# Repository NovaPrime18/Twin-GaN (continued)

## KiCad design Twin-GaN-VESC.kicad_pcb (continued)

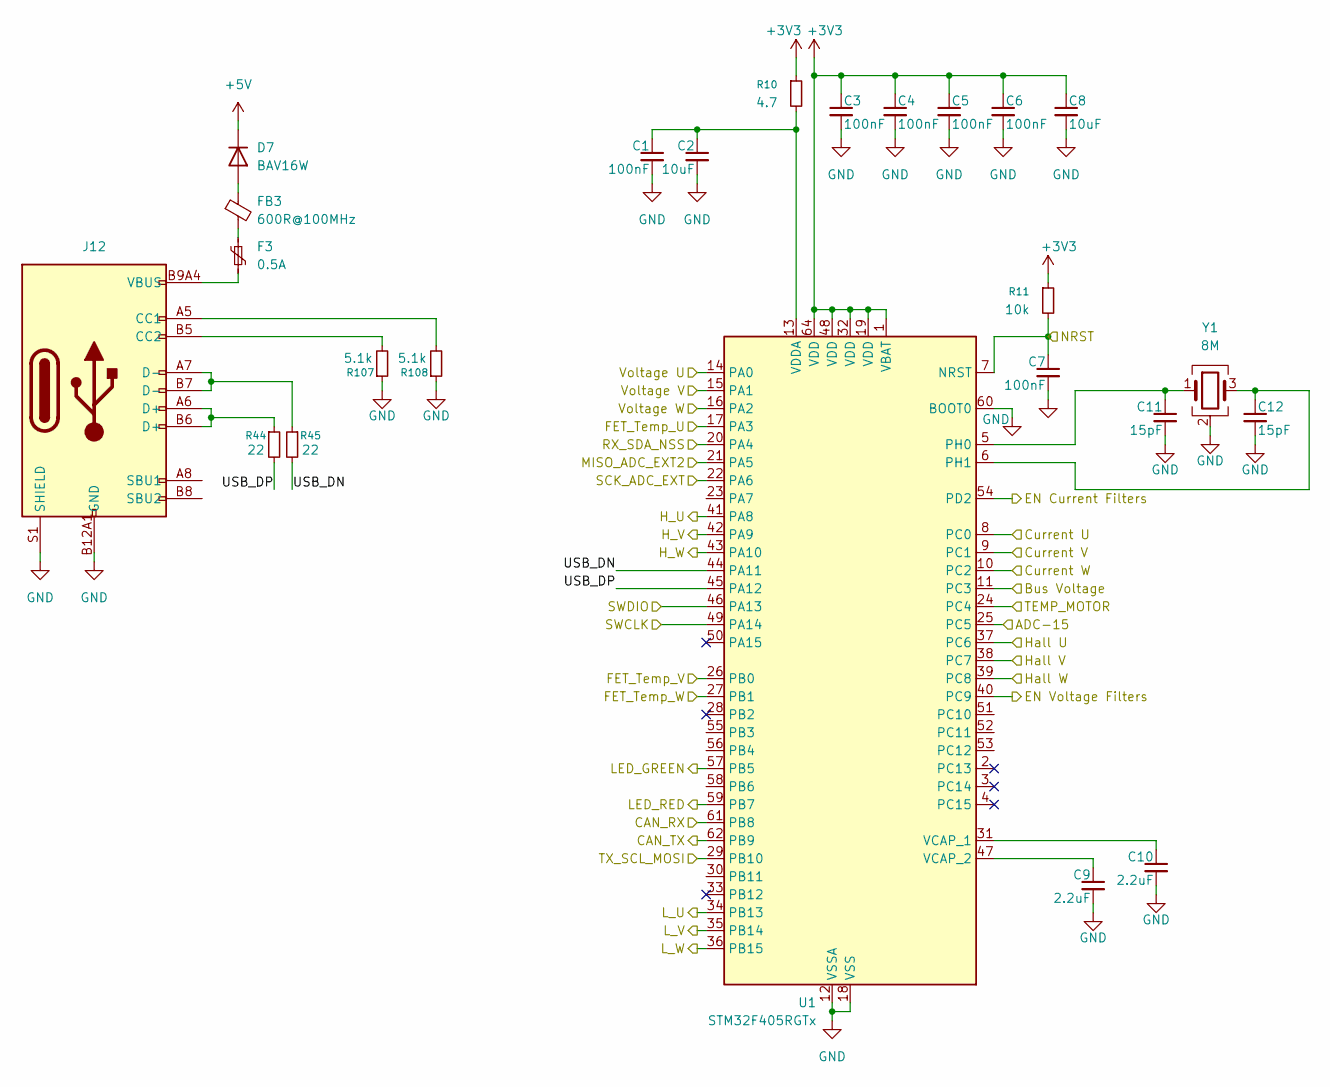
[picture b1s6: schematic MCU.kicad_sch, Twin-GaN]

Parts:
C1, C3, C4, C5, C6, C7: 100nF; C_0402_1005Metric; LCSC C307331
C2, C8: 10uF; C_0805_2012Metric; LCSC C440198
C9, C10: 2.2uF; C_0402_1005Metric; LCSC C20539421
C11, C12: 15pF; C_0402_1005Metric; LCSC C1548
D7: BAV16W; D_SOD-123; JLC C459527
F3: 0.5A; R_0805_2012Metric; JLC C2833485
FB3: 600R@100MHz; L_0402_1005Metric; LCSC C76884
J12: Connector, USB-TYPE-C-16P; TYPE-C-SMD_HX-TYPE-C-16PIN; LCSC C2927039
R10: 4.7; R_0402_1005Metric; LCSC C25121
R11: 10k; R_0402_1005Metric; LCSC C25744
R44, R45: 22; R_0402_1005Metric; LCSC C25092
R107, R108: 5.1k; R_0402_1005Metric; LCSC C25905
U1: STM32F405RGTx; LQFP-64_10x10mm_P0.5mm; LCSC C15742
Y1: 8M; Crystal_SMD_3225-4Pin_3.2x2.5mm; JLC C2682775

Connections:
+3V3: C3.1, C4.1, C5.1, C6.1, C8.1, R10.1, R11.1, U1.1 (VBAT), U1.19 (VDD), U1.32 (VDD), U1.48 (VDD), U1.64 (VDD); also elsewhere on the board
+5V: D7.1 (K); also elsewhere on the board
/Bus Voltage: U1.11 (PC3); also elsewhere on the board
/CAN1/RX: U1.61 (PB8); also elsewhere on the board
/CAN1/TX: U1.62 (PB9); also elsewhere on the board
/Filters/Curr_U_Out: U1.8 (PC0); also elsewhere on the board
/Filters/Curr_V_Out: U1.9 (PC1); also elsewhere on the board
/Filters/Curr_W_Out: U1.10 (PC2); also elsewhere on the board
/Filters/EN_C: U1.54 (PD2); also elsewhere on the board
/Filters/EN_V: U1.40 (PC9); also elsewhere on the board
/Filters/Volt_U_In: U1.14 (PA0); also elsewhere on the board
/Filters/Volt_V_In: U1.15 (PA1); also elsewhere on the board
/Filters/Volt_W_In: U1.16 (PA2); also elsewhere on the board
/MCU/ADC-15: U1.25 (PC5); also elsewhere on the board
/MCU/FET_Temp_U: U1.17 (PA3); also elsewhere on the board
/MCU/FET_Temp_V: U1.26 (PB0); also elsewhere on the board
/MCU/FET_Temp_W: U1.27 (PB1); also elsewhere on the board
/MCU/H_U: U1.41 (PA8); also elsewhere on the board
/MCU/H_V: U1.42 (PA9); also elsewhere on the board
/MCU/H_W: U1.43 (PA10); also elsewhere on the board
/MCU/Hall U: U1.37 (PC6); also elsewhere on the board
/MCU/Hall V: U1.38 (PC7); also elsewhere on the board
/MCU/Hall W: U1.39 (PC8); also elsewhere on the board
/MCU/LED_GREEN: U1.57 (PB5); also elsewhere on the board
/MCU/LED_RED: U1.59 (PB7); also elsewhere on the board
/MCU/L_U: U1.34 (PB13); also elsewhere on the board
/MCU/L_V: U1.35 (PB14); also elsewhere on the board
/MCU/L_W: U1.36 (PB15); also elsewhere on the board
/MCU/MISO_ADC_EXT2: U1.21 (PA5); also elsewhere on the board
/MCU/NRST: C7.1, R11.2, U1.7 (NRST); also elsewhere on the board
/MCU/RX_SDA_NSS: U1.20 (PA4); also elsewhere on the board
/MCU/SCK_ADC_EXT: U1.22 (PA6); also elsewhere on the board
/MCU/SWCLK: U1.49 (PA14); also elsewhere on the board
/MCU/SWDIO: U1.46 (PA13); also elsewhere on the board
/MCU/TEMP_MOTOR: U1.24 (PC4); also elsewhere on the board
/MCU/TX_SCL_MOSI: U1.29 (PB10); also elsewhere on the board
/MCU/USB_DN: R45.2, U1.44 (PA11)
/MCU/USB_DP: R44.2, U1.45 (PA12)
GND: C1.2, C2.2, C3.2, C4.2, C5.2, C6.2, C7.2, C8.2, C9.2, C10.2, C11.2, C12.2, J12.A12B1 (GND), J12.B12A1 (GND), J12.S1 (SHIELD), R107.1, R108.1, U1.12 (VSSA), U1.18 (VSS), U1.60 (BOOT0), U1.63 (VSS), Y1.2 (G), Y1.4 (G); also elsewhere on the board
unnamed: D7.2 (A), FB3.1
unnamed: F3.1, FB3.2
unnamed: F3.2, J12.A9B4 (VBUS), J12.B9A4 (VBUS)
unnamed: J12.A5 (CC1), R108.2
unnamed: J12.B5 (CC2), R107.2
unnamed: J12.A6 (D+), J12.B6 (D+), R44.1
unnamed: J12.A7 (D-), J12.B7 (D-), R45.1
unnamed: C11.1, U1.5 (PH0), Y1.1
unnamed: C12.1, U1.6 (PH1), Y1.3
unnamed: C10.1, U1.31 (VCAP_1)
unnamed: C9.1, U1.47 (VCAP_2)
unnamed: C1.1, C2.1, R10.2, U1.13 (VDDA)

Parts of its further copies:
C16, C36, C37, C38, C39, C40: 100nF; C_0402_1005Metric; LCSC C307331
C17, C41: 10uF; C_0805_2012Metric; LCSC C440198
C42, C43: 2.2uF; C_0402_1005Metric; LCSC C20539421
C44, C45: 15pF; C_0402_1005Metric; LCSC C1548
D8: BAV16W; D_SOD-123; JLC C459527
F4: 0.5A; R_0805_2012Metric; JLC C2833485
FB4: 600R@100MHz; L_0402_1005Metric; LCSC C76884
J13: Connector, USB-TYPE-C-16P; TYPE-C-SMD_HX-TYPE-C-16PIN; LCSC C2927039
R30: 4.7; R_0402_1005Metric; LCSC C25121
R31: 10k; R_0402_1005Metric; LCSC C25744
R46, R47: 22; R_0402_1005Metric; LCSC C25092
R109, R110: 5.1k; R_0402_1005Metric; LCSC C25905
U4: STM32F405RGTx; LQFP-64_10x10mm_P0.5mm; LCSC C15742
Y2: 8M; Crystal_SMD_3225-4Pin_3.2x2.5mm; JLC C2682775

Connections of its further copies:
+3V3: C36.1, C37.1, C38.1, C39.1, C41.1, R30.1, R31.1, U4.1 (VBAT), U4.19 (VDD), U4.32 (VDD), U4.48 (VDD), U4.64 (VDD); also elsewhere on the board
+5V: D8.1 (K); also elsewhere on the board
/Bus Voltage: U4.11 (PC3); also elsewhere on the board
/CAN2/RX: U4.61 (PB8); also elsewhere on the board
/CAN2/TX: U4.62 (PB9); also elsewhere on the board
/Filters1/Curr_U_Out: U4.8 (PC0); also elsewhere on the board
/Filters1/Curr_V_Out: U4.9 (PC1); also elsewhere on the board
/Filters1/Curr_W_Out: U4.10 (PC2); also elsewhere on the board
/Filters1/EN_C: U4.54 (PD2); also elsewhere on the board
/Filters1/EN_V: U4.40 (PC9); also elsewhere on the board
/Filters1/Volt_U_In: U4.14 (PA0); also elsewhere on the board
/Filters1/Volt_V_In: U4.15 (PA1); also elsewhere on the board
/Filters1/Volt_W_In: U4.16 (PA2); also elsewhere on the board
/MCU1/ADC-15: U4.25 (PC5); also elsewhere on the board
/MCU1/FET_Temp_U: U4.17 (PA3); also elsewhere on the board
/MCU1/FET_Temp_V: U4.26 (PB0); also elsewhere on the board
/MCU1/FET_Temp_W: U4.27 (PB1); also elsewhere on the board
/MCU1/H_U: U4.41 (PA8); also elsewhere on the board
/MCU1/H_V: U4.42 (PA9); also elsewhere on the board
/MCU1/H_W: U4.43 (PA10); also elsewhere on the board
/MCU1/Hall U: U4.37 (PC6); also elsewhere on the board
/MCU1/Hall V: U4.38 (PC7); also elsewhere on the board
/MCU1/Hall W: U4.39 (PC8); also elsewhere on the board
/MCU1/LED_GREEN: U4.57 (PB5); also elsewhere on the board
/MCU1/LED_RED: U4.59 (PB7); also elsewhere on the board
/MCU1/L_U: U4.34 (PB13); also elsewhere on the board
/MCU1/L_V: U4.35 (PB14); also elsewhere on the board
/MCU1/L_W: U4.36 (PB15); also elsewhere on the board
/MCU1/MISO_ADC_EXT2: U4.21 (PA5); also elsewhere on the board
/MCU1/NRST: C40.1, R31.2, U4.7 (NRST); also elsewhere on the board
/MCU1/RX_SDA_NSS: U4.20 (PA4); also elsewhere on the board
/MCU1/SCK_ADC_EXT: U4.22 (PA6); also elsewhere on the board
/MCU1/SWCLK: U4.49 (PA14); also elsewhere on the board
/MCU1/SWDIO: U4.46 (PA13); also elsewhere on the board
/MCU1/TEMP_MOTOR: U4.24 (PC4); also elsewhere on the board
/MCU1/TX_SCL_MOSI: U4.29 (PB10); also elsewhere on the board
/MCU1/USB_DN: R47.2, U4.44 (PA11)
/MCU1/USB_DP: R46.2, U4.45 (PA12)
GND: C16.2, C17.2, C36.2, C37.2, C38.2, C39.2, C40.2, C41.2, C42.2, C43.2, C44.2, C45.2, J13.A12B1 (GND), J13.B12A1 (GND), J13.S1 (SHIELD), R109.1, R110.1, U4.12 (VSSA), U4.18 (VSS), U4.60 (BOOT0), U4.63 (VSS), Y2.2 (G), Y2.4 (G); also elsewhere on the board
unnamed: D8.2 (A), FB4.1
unnamed: F4.1, FB4.2
unnamed: F4.2, J13.A9B4 (VBUS), J13.B9A4 (VBUS)
unnamed: J13.A5 (CC1), R110.2
unnamed: J13.B5 (CC2), R109.2
unnamed: J13.A6 (D+), J13.B6 (D+), R46.1
unnamed: J13.A7 (D-), J13.B7 (D-), R47.1
unnamed: C44.1, U4.5 (PH0), Y2.1
unnamed: C45.1, U4.6 (PH1), Y2.3
unnamed: C43.1, U4.31 (VCAP_1)
unnamed: C42.1, U4.47 (VCAP_2)
unnamed: C16.1, C17.1, R30.2, U4.13 (VDDA)

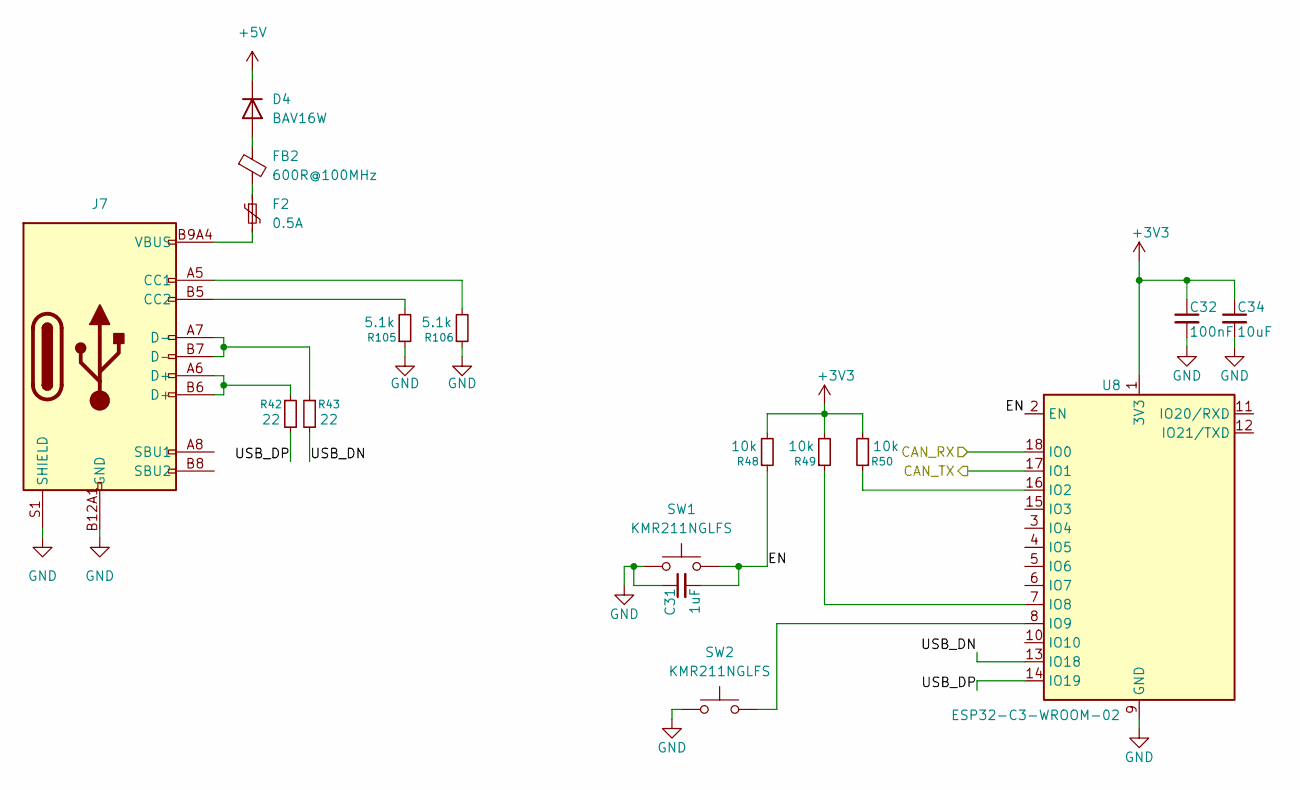
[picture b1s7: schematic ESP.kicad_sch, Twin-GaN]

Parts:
C31: 1uF; C_0402_1005Metric; LCSC C52923
C32: 100nF; C_0402_1005Metric; LCSC C307331
C34: 10uF; C_0805_2012Metric; LCSC C440198
D4: BAV16W; D_SOD-123; JLC C459527
F2: 0.5A; R_0805_2012Metric; JLC C2833485
FB2: 600R@100MHz; L_0402_1005Metric; LCSC C76884
J7: Connector, USB-TYPE-C-16P; TYPE-C-SMD_HX-TYPE-C-16PIN; LCSC C2927039
R42, R43: 22; R_0402_1005Metric; LCSC C25092
R48, R49, R50: 10k; R_0402_1005Metric; LCSC C25744
R105, R106: 5.1k; R_0402_1005Metric; LCSC C25905
SW1, SW2: KMR211NGLFS; SW_Push_1P1T_NO_CK_KMR2; JLC C221676
U8: ESP32-C3-WROOM-02; JLC C2934560

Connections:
+3V3: C32.1, C34.1, R48.2, R49.2, R50.2, U8.1 (3V3); also elsewhere on the board
+5V: D4.1 (K); also elsewhere on the board
/CAN/RX: U8.18 (IO0); also elsewhere on the board
/CAN/TX: U8.17 (IO1); also elsewhere on the board
/ESP/EN: C31.2, R48.1, SW1.2, U8.2 (EN)
/ESP/USB_DN: R43.2, U8.13 (IO18)
/ESP/USB_DP: R42.2, U8.14 (IO19)
GND: C31.1, C32.2, C34.2, J7.A12B1 (GND), J7.B12A1 (GND), J7.S1 (SHIELD), R105.1, R106.1, SW1.1, SW2.1, U8.9 (GND), U8.19 (GND); also elsewhere on the board
unnamed: D4.2 (A), FB2.1
unnamed: F2.1, FB2.2
unnamed: F2.2, J7.A9B4 (VBUS), J7.B9A4 (VBUS)
unnamed: J7.A5 (CC1), R106.2
unnamed: J7.B5 (CC2), R105.2
unnamed: J7.A6 (D+), J7.B6 (D+), R42.1
unnamed: J7.A7 (D-), J7.B7 (D-), R43.1
unnamed: R50.1, U8.16 (IO2)
unnamed: R49.1, U8.7 (IO8)
unnamed: SW2.2, U8.8 (IO9)

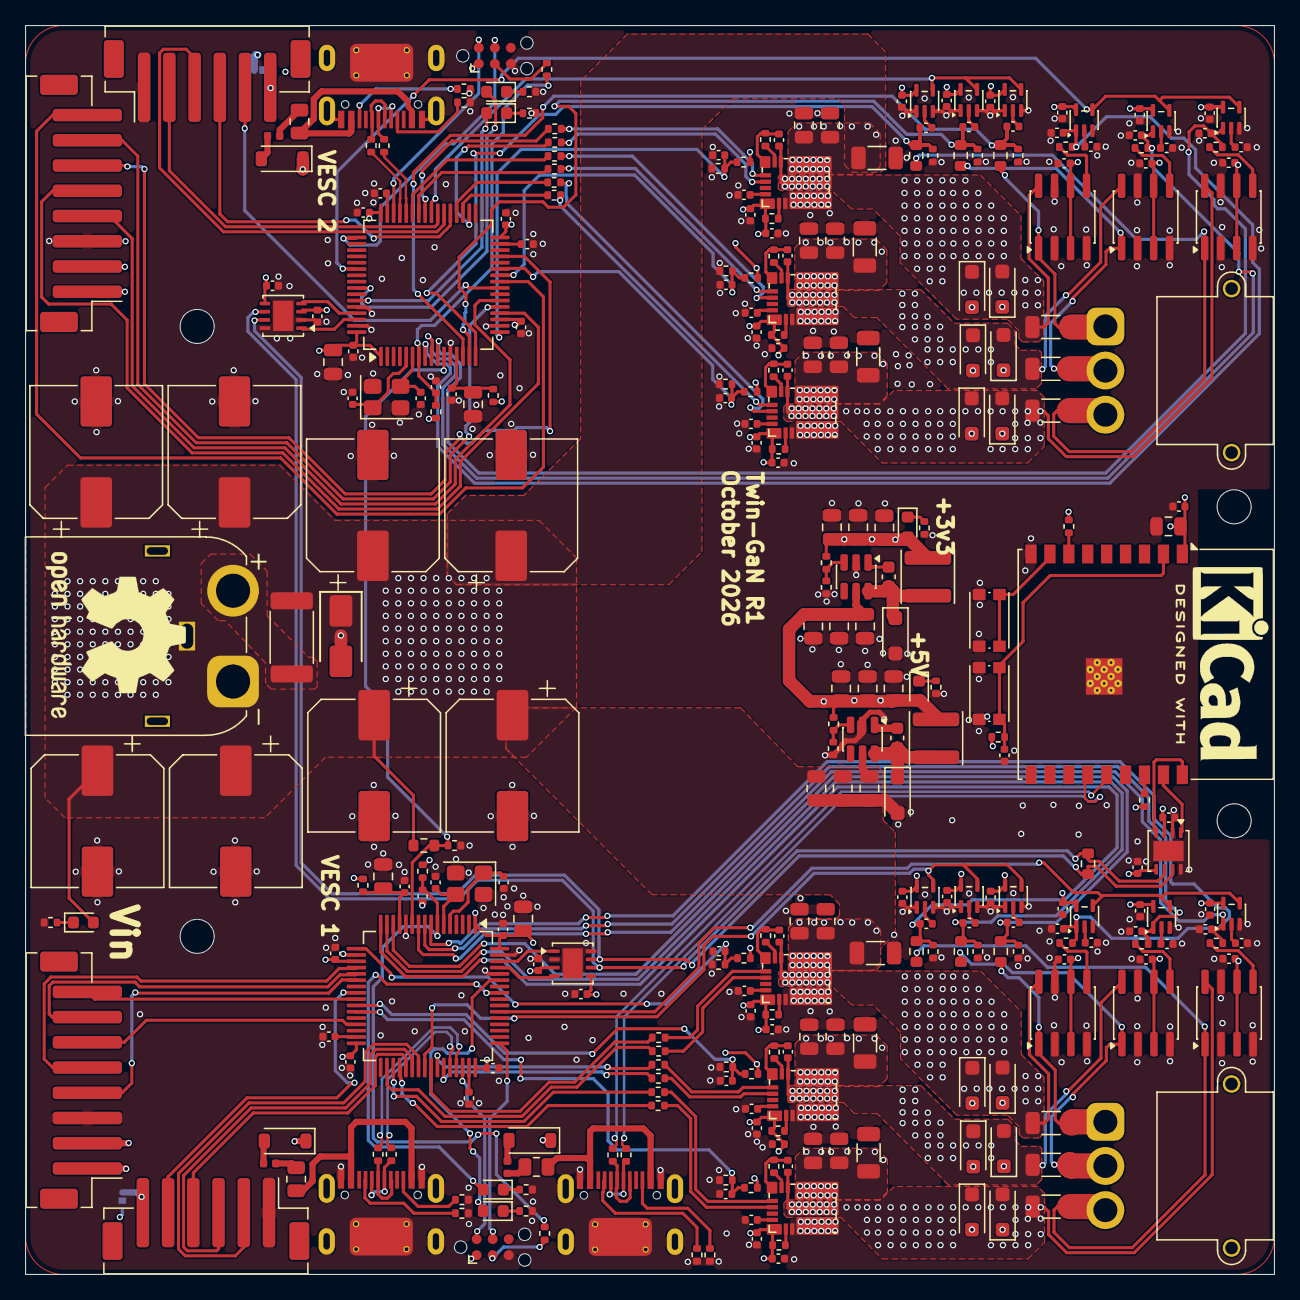
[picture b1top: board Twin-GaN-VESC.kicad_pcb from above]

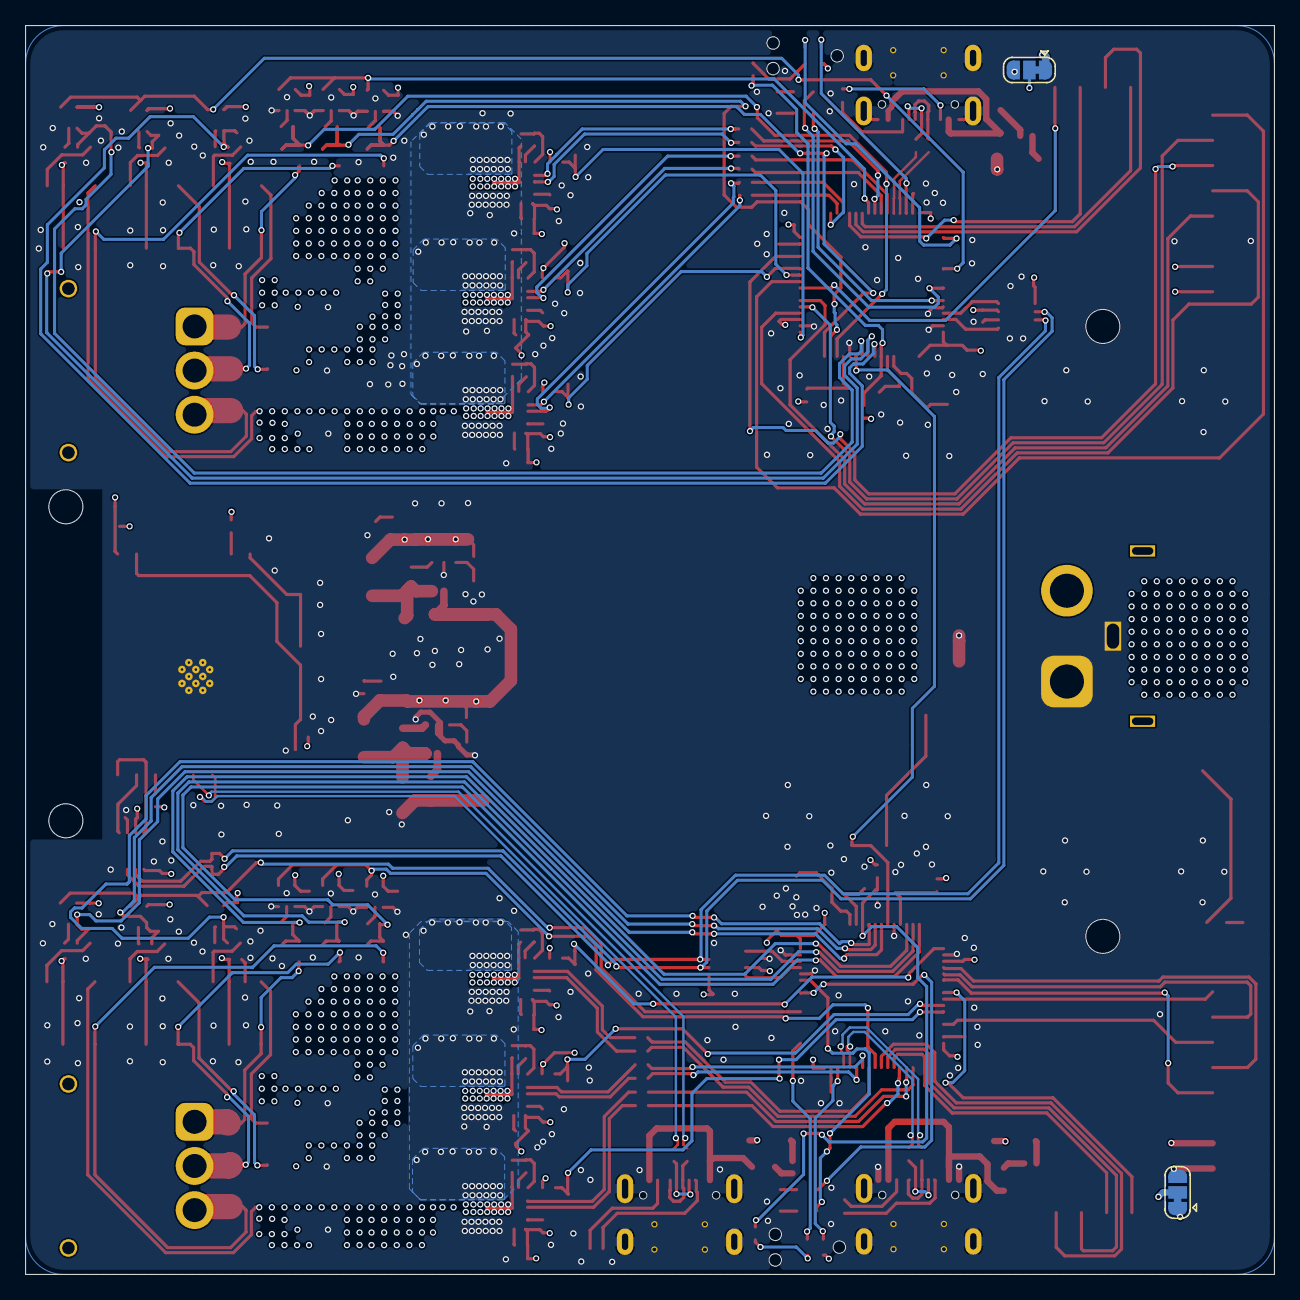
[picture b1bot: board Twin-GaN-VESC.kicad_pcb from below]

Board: 4 copper layers, 99.0 x 99.0 mm, 322 parts (2 on the bottom side), 200 nets.

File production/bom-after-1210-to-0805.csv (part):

"Reference","Value","Footprint","LCSC","Manufacturer Part Number"
"C1","100nF","Capacitor_SMD:C_0402_1005Metric","C307331",""
"C2","10uF","Capacitor_SMD:C_0805_2012Metric","C440198",""
"C3","100nF","Capacitor_SMD:C_0402_1005Metric","C307331",""
"C4","100nF","Capacitor_SMD:C_0402_1005Metric","C307331",""
"C5","100nF","Capacitor_SMD:C_0402_1005Metric","C307331",""
"C6","100nF","Capacitor_SMD:C_0402_1005Metric","C307331",""
"C7","100nF","Capacitor_SMD:C_0402_1005Metric","C307331",""
"C8","10uF","Capacitor_SMD:C_0805_2012Metric","C440198",""
"C9","2.2uF","Capacitor_SMD:C_0402_1005Metric","C20539421",""
"C10","2.2uF","Capacitor_SMD:C_0402_1005Metric","C20539421",""
"C11","15pF","Capacitor_SMD:C_0402_1005Metric","C1548",""
"C12","15pF","Capacitor_SMD:C_0402_1005Metric","C1548",""
"C13","2.2uF","Capacitor_SMD:C_0402_1005Metric","C20539421",""
"C14","2.2uF 100V","Capacitor_SMD:C_1206_3216Metric","C170101",""
"C15","100nF","Capacitor_SMD:C_0402_1005Metric","C307331",""
"C16","100nF","Capacitor_SMD:C_0402_1005Metric","C307331",""
"C17","10uF","Capacitor_SMD:C_0805_2012Metric","C440198",""
"C18","100nF","Capacitor_SMD:C_0402_1005Metric","C307331",""
"C19","2.2uF","Capacitor_SMD:C_0402_1005Metric","C20539421",""
"C20","100nF","Capacitor_SMD:C_0402_1005Metric","C307331",""
"C21","2.2uF 100V","Capacitor_SMD:C_1206_3216Metric","C170101",""
"C22","100nF","Capacitor_SMD:C_0402_1005Metric","C307331",""
"C23","2.2uF","Capacitor_SMD:C_0402_1005Metric","C20539421",""
"C24","100nF","Capacitor_SMD:C_0402_1005Metric","C307331",""
"C25","2.2uF 100V","Capacitor_SMD:C_1206_3216Metric","C170101",""
"C26","100nF","Capacitor_SMD:C_0402_1005Metric","C307331",""
"C27","2.2uF","Capacitor_SMD:C_0402_1005Metric","C20539421",""
"C28","2.2uF","Capacitor_SMD:C_0402_1005Metric","C20539421",""
"C29","100nF","Capacitor_SMD:C_0402_1005Metric","C307331",""
"C30","100nF","Capacitor_SMD:C_0402_1005Metric","C307331",""
"C31","1uF","Capacitor_SMD:C_0402_1005Metric","C52923",""
"C32","100nF","Capacitor_SMD:C_0402_1005Metric","C307331",""
"C34","10uF","Capacitor_SMD:C_0805_2012Metric","C440198",""
"C35","2.2uF","Capacitor_SMD:C_0402_1005Metric","C20539421",""
"C36","100nF","Capacitor_SMD:C_0402_1005Metric","C307331",""
"C37","100nF","Capacitor_SMD:C_0402_1005Metric","C307331",""
"C38","100nF","Capacitor_SMD:C_0402_1005Metric","C307331",""
"C39","100nF","Capacitor_SMD:C_0402_1005Metric","C307331",""
"C40","100nF","Capacitor_SMD:C_0402_1005Metric","C307331",""
"C41","10uF","Capacitor_SMD:C_0805_2012Metric","C440198",""
"C42","2.2uF","Capacitor_SMD:C_0402_1005Metric","C20539421",""
"C43","2.2uF","Capacitor_SMD:C_0402_1005Metric","C20539421",""
"C44","15pF","Capacitor_SMD:C_0402_1005Metric","C1548",""
"C45","15pF","Capacitor_SMD:C_0402_1005Metric","C1548",""
"C46","2.2uF","Capacitor_SMD:C_0402_1005Metric","C20539421",""
"C47","100nF","Capacitor_SMD:C_0402_1005Metric","C307331",""
"C48","15nF","Capacitor_SMD:C_0402_1005Metric","C114405",""
"C49","1nF","Capacitor_SMD:C_0402_1005Metric","C1523",""
"C50","100nF","Capacitor_SMD:C_0402_1005Metric","C307331",""
"C51","100nF","Capacitor_SMD:C_0402_1005Metric","C307331",""
"C52","100nF","Capacitor_SMD:C_0402_1005Metric","C307331",""
"C53","100nF","Capacitor_SMD:C_0402_1005Metric","C307331",""
"C54","15nF","Capacitor_SMD:C_0402_1005Metric","C114405",""
"C55","100n X7R 100V","Capacitor_SMD:C_0603_1608Metric","C15725","CL10B104KC8NNNC"
"C56","1u X7R 100V","Capacitor_SMD:C_0805_2012Metric","C5370002","CC0805KKX7R0BB105"
"C57","15nF","Capacitor_SMD:C_0402_1005Metric","C114405",""
"C58","100nF","Capacitor_SMD:C_0402_1005Metric","C307331",""
"C59","1nF","Capacitor_SMD:C_0402_1005Metric","C1523",""
"C60","100nF","Capacitor_SMD:C_0402_1005Metric","C307331",""
"C61","1u X7R 100V","Capacitor_SMD:C_0805_2012Metric","C5370002","CC0805KKX7R0BB105"
"C62","1u X7R 100V","Capacitor_SMD:C_0805_2012Metric","C5370002","CC0805KKX7R0BB105"
"C63","100nF","Capacitor_SMD:C_0402_1005Metric","C307331",""
"C64","1u X7R 100V","Capacitor_SMD:C_0805_2012Metric","C5370002","CC0805KKX7R0BB105"
"C65","10u X7R 25V","Capacitor_SMD:C_0805_2012Metric","C3039694","CL21B106KAYQNNE"
"C66","15nF","Capacitor_SMD:C_0402_1005Metric","C114405",""
"C67","1nF","Capacitor_SMD:C_0402_1005Metric","C1523",""
"C68","1nF","Capacitor_SMD:C_0402_1005Metric","C1523",""
"C69","10u X7R 25V","Capacitor_SMD:C_0805_2012Metric","C3039694","CL21B106KAYQNNE"
"C70","100nF","Capacitor_SMD:C_0402_1005Metric","C307331",""
"C71","100nF","Capacitor_SMD:C_0402_1005Metric","C307331",""
"C72","10u X7R 25V","Capacitor_SMD:C_0805_2012Metric","C3039694","CL21B106KAYQNNE"
"C73","100nF","Capacitor_SMD:C_0402_1005Metric","C307331",""
"C74","100nF","Capacitor_SMD:C_0402_1005Metric","C307331",""
"C75","15nF","Capacitor_SMD:C_0402_1005Metric","C114405",""
"C76","100nF","Capacitor_SMD:C_0402_1005Metric","C307331",""
"C77","100nF","Capacitor_SMD:C_0402_1005Metric","C307331",""
"C78","1nF","Capacitor_SMD:C_0402_1005Metric","C1523",""
"C79","100nF","Capacitor_SMD:C_0402_1005Metric","C307331",""
"C80","100nF","Capacitor_SMD:C_0402_1005Metric","C307331",""
"C81","15nF","Capacitor_SMD:C_0402_1005Metric","C114405",""
"C82","1nF","Capacitor_SMD:C_0402_1005Metric","C1523",""
"C83","100nF","Capacitor_SMD:C_0402_1005Metric","C307331",""
"C84","100nF","Capacitor_SMD:C_0402_1005Metric","C307331",""
"C85","2.2uF","Capacitor_SMD:C_0402_1005Metric","C20539421",""
"C86","1u X7R 100V","Capacitor_SMD:C_0805_2012Metric","C5370002","CC0805KKX7R0BB105"
"C87","1u X7R 100V","Capacitor_SMD:C_0805_2012Metric","C5370002","CC0805KKX7R0BB105"
"C88","1u X7R 100V","Capacitor_SMD:C_0805_2012Metric","C5370002","CC0805KKX7R0BB105"
"C89","2.2uF","Capacitor_SMD:C_0402_1005Metric","C20539421",""
"C90","100n X7R 100V","Capacitor_SMD:C_0603_1608Metric","C15725","CL10B104KC8NNNC"
"C91","10u X7R 25V","Capacitor_SMD:C_0805_2012Metric","C3039694","CL21B106KAYQNNE"
"C92","10u X7R 25V","Capacitor_SMD:C_0805_2012Metric","C3039694","CL21B106KAYQNNE"
"C93","10u X7R 25V","Capacitor_SMD:C_0805_2012Metric","C3039694","CL21B106KAYQNNE"
"C94","2.2uF","Capacitor_SMD:C_0402_1005Metric","C20539421",""
"C95","2.2uF","Capacitor_SMD:C_0402_1005Metric","C20539421",""
"C96","2.2uF","Capacitor_SMD:C_0402_1005Metric","C20539421",""
"C97","100nF","Capacitor_SMD:C_0402_1005Metric","C307331",""
"C98","100nF","Capacitor_SMD:C_0402_1005Metric","C307331",""
"C99","100nF","Capacitor_SMD:C_0402_1005Metric","C307331",""
"C100","2.2uF 100V","Capacitor_SMD:C_1206_3216Metric","C170101",""
"C101","2.2uF 100V","Capacitor_SMD:C_1206_3216Metric","C170101",""
"C102","2.2uF 100V","Capacitor_SMD:C_1206_3216Metric","C170101",""
"C103","100nF","Capacitor_SMD:C_0402_1005Metric","C307331",""
"C104","100nF","Capacitor_SMD:C_0402_1005Metric","C307331",""
"C105","100nF","Capacitor_SMD:C_0402_1005Metric","C307331",""
"C106","100nF","Capacitor_SMD:C_0402_1005Metric","C307331",""
"C107","100nF","Capacitor_SMD:C_0402_1005Metric","C307331",""
"C108","100nF","Capacitor_SMD:C_0402_1005Metric","C307331",""
"C109","100nF","Capacitor_SMD:C_0402_1005Metric","C307331",""
"C110","100uF 80V","Capacitor_SMD:CP_Elec_10x10","C487410",""
"C111","100uF 80V","Capacitor_SMD:CP_Elec_10x10","C487410",""
"C112","100uF 80V","Capacitor_SMD:CP_Elec_10x10","C487410",""
"C113","100uF 80V","Capacitor_SMD:CP_Elec_10x10","C487410",""
"C115","100uF 80V","Capacitor_SMD:CP_Elec_10x10","C487410",""
"C116","100uF 80V","Capacitor_SMD:CP_Elec_10x10","C487410",""
"C117","100uF 80V","Capacitor_SMD:CP_Elec_10x10","C487410",""
"C118","100uF 80V","Capacitor_SMD:CP_Elec_10x10","C487410",""
"D1","Red","LED_SMD:LED_0603_1608Metric","C2286",""
"D2","Green","LED_SMD:LED_0603_1608Metric","C84267",""
"D4","BAV16W","Diode_SMD:D_SOD-123","C459527",""
"D5","Red","LED_SMD:LED_0603_1608Metric","C2286",""
"D6","Green","LED_SMD:LED_0603_1608Metric","C84267",""
"D7","BAV16W","Diode_SMD:D_SOD-123","C459527",""
"D8","BAV16W","Diode_SMD:D_SOD-123","C459527",""
"D14","MBR1H100SFT3G","Diode_SMD:D_SOD-123F","C235757","MBR1H100SFT3G"
"D22","LED","LED_SMD:LED_0603_1608Metric","C2286",""
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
